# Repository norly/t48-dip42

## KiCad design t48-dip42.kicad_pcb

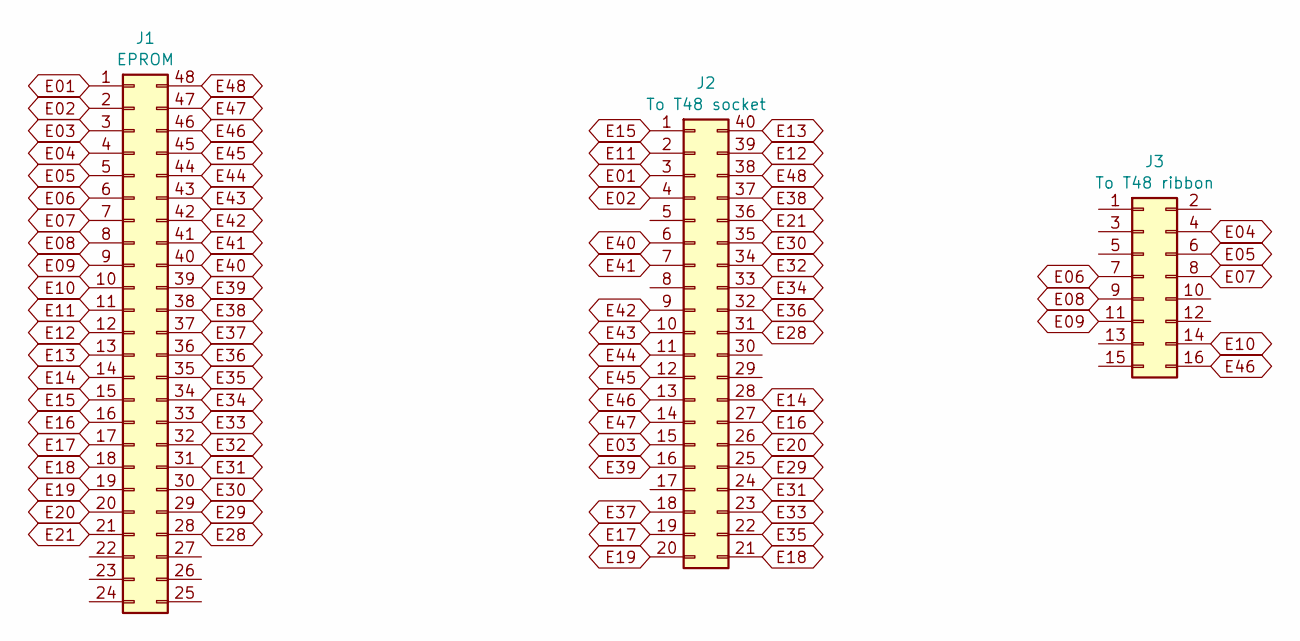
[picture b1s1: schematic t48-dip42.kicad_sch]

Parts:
J1: EPROM; DIP-48_W15.24mm_Socket_LongPads
J2: To T48 socket; DIP-40_W15.24mm_Socket_LongPads
J3: To T48 ribbon; PinHeader_2x08_P2.54mm_Horizontal

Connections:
E01: J1.1, J2.3
E02: J1.2, J2.4
E03: J1.3, J2.15
E04: J1.4, J3.4
E05: J1.5, J3.6
E06: J1.6, J3.7
E07: J1.7, J3.8
E08: J1.8, J3.9
E09: J1.9, J3.11
E10: J1.10, J3.14
E11: J1.11, J2.2
E12: J1.12, J2.39
E13: J1.13, J2.40
E14: J1.14, J2.28
E15: J1.15, J2.1
E16: J1.16, J2.27
E17: J1.17, J2.19
E18: J1.18, J2.21
E19: J1.19, J2.20
E20: J1.20, J2.26
E21: J1.21, J2.36
E28: J1.28, J2.31
E29: J1.29, J2.25
E30: J1.30, J2.35
E31: J1.31, J2.24
E32: J1.32, J2.34
E33: J1.33, J2.23
E34: J1.34, J2.33
E35: J1.35, J2.22
E36: J1.36, J2.32
E37: J1.37, J2.18
E38: J1.38, J2.37
E39: J1.39, J2.16
E40: J1.40, J2.6
E41: J1.41, J2.7
E42: J1.42, J2.9
E43: J1.43, J2.10
E44: J1.44, J2.11
E45: J1.45, J2.12
E46: J1.46, J2.13, J3.16
E47: J1.47, J2.14
E48: J1.48, J2.38

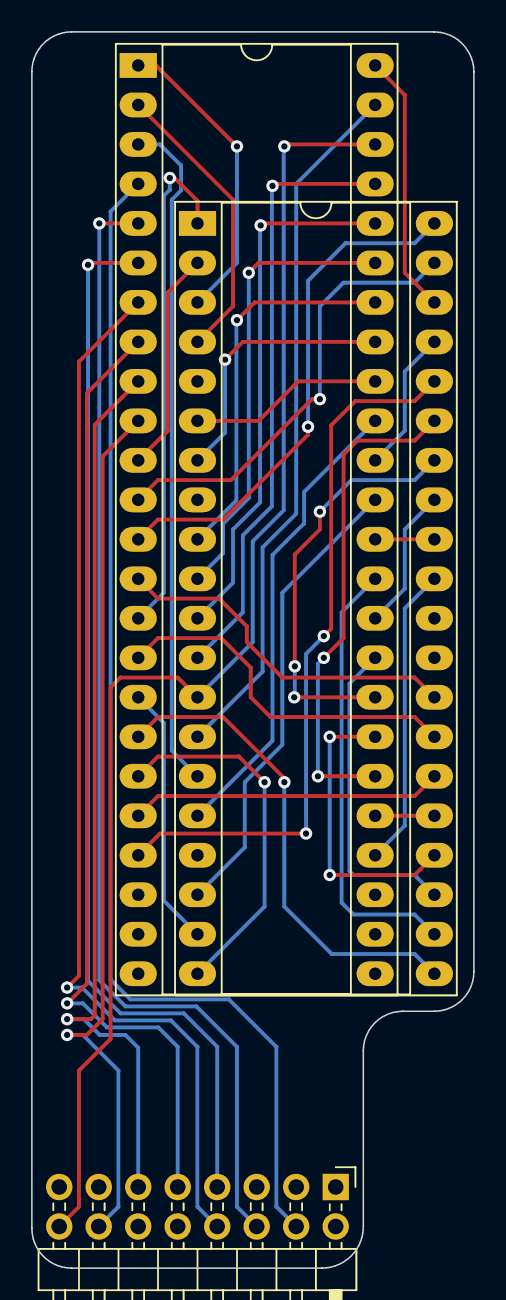
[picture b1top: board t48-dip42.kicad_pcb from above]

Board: 2 copper layers, 28.4 x 79.5 mm, 3 parts (0 on the bottom side), 42 nets.

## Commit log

2023-12-01 Add .gitignore
2023-12-01 v01: Initial version
2023-12-01 v02: Move ribbon cable pins down to make room for test socket
2024-01-01 v03: Fix swapped upper/lower pins on ribbon cable
2024-02-15 LICENSE: CC0
